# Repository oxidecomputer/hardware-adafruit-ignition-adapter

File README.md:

# hardware-adafruit-ignition-adapter

## Description

Adapter board for the [Adafruit FT232H](https://www.adafruit.com/product/2264)
compatible with `iceprog` and the Samtec debug pinout we're using on our
designs.

## Ordering Information

Each release contains a file called `[CPN]_release_notes.txt` with ordering
instructions. Order PCBs through Sierra Circuits' [Turnkey
PRO](https://www.protoexpress.com/products/turnkey-pro/) fabrication and
assembly service.

## Release Information

Fabrication data follows the `[CPN]_rev[X]_v[Y]` naming convention, where
revision `rev[X]` and version `v[Y]` corresponds to the two numbers in Altium's
release version. Here's why:

- When we release the board in Altium 365, Altium tags the release with the
  suffix `[X].[Y]`

- However, Sierra Circuits only accepts a single revision number, which appears
  in their ordering system as `_rev[X]`.
  
- When we assemble the tapeout data package together for Sierra Circuits, we
  name the tapeout files `[CPN]_rev[X]_v[Y]` to maintain the mapping between
  Altium release and the out-of-band tapeout data package.

- When we order PCBs through Sierra Circuits, we specify the revision using the
  `[X]` number. This appears in Sierra's order system as `[CPN]_rev[X]`.

Essentially, we ignore the `[Y]` value and we increment the `[X]` in the Altium
release. In practice, however, the `[Y]` value in the Altium release ends up
getting incremented if we have to re-release something in Altium to correct data
export errors before submitting the release for fabrication (for example, to fix
missing drill files in the tapeout data package). If this sounds confusing, it's
because it is.

## Assembly

Follow the [assembly
instructions](https://github.com/oxidecomputer/hardware-adafruit-ignition-adapter/tree/main/assembly)
to assemble a complete Ignition programming dongle.

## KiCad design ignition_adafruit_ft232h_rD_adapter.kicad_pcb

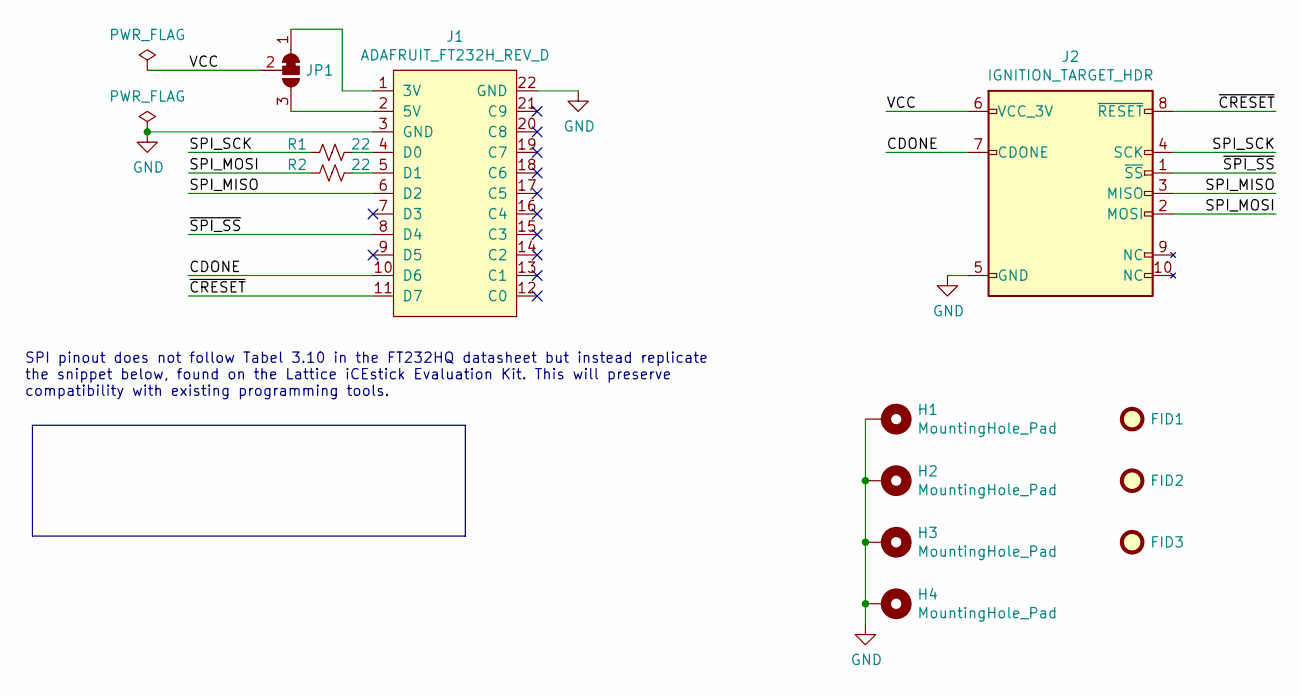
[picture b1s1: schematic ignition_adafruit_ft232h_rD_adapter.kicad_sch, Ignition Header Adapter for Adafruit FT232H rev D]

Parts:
FID1, FID3: Fiducial; Fiducial_0.5mm_Mask1mm
FID2: iCE40 Adapter; Oxide_Board_Identifier_23x6mm
H1, H2, H3, H4: MountingHole_Pad; MountingHole_100mils_Pad
J1: ADAFRUIT_FT232H_REV_D; ADAFRUIT_FT232H_REVD
J2: IGNITION_TARGET_HDR; TFC-105-02-F-D-A-K
JP1: SolderJumper_3_Bridged12; SolderJumper-3_P1.3mm_Bridged12_Pad1.0x1.5mm
R1, R2: 22; R_0603_1608Metric

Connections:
/CDONE: J1.10 (D6), J2.7 (CDONE)
/SPI_MISO: J1.6 (D2), J2.3 (MISO)
/SPI_MOSI: J2.2 (MOSI), R2.2
/SPI_SCK: J2.4 (SCK), R1.2
/VCC: J2.6 (VCC_3V), JP1.2 (C)
/~CRESET: J1.11 (D7), J2.8 (~RESET)
/~SPI_SS: J1.8 (D4), J2.1 (~SS)
GND: H1.1, H2.1, H3.1, H4.1, J1.3 (GND), J1.22 (GND), J2.5 (GND)
unnamed: J1.1 (3V), JP1.1 (A)
unnamed: J1.2 (5V), JP1.3 (B)
unnamed: J1.4 (D0), R1.1
unnamed: J1.5 (D1), R2.1

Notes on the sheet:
SPI pinout does not follow Tabel 3.10 in the FT232HQ datasheet but instead replicate the snippet below, found on the Lattice iCEstick Evaluation Kit. This will preserve compatibility with existing programming tools.

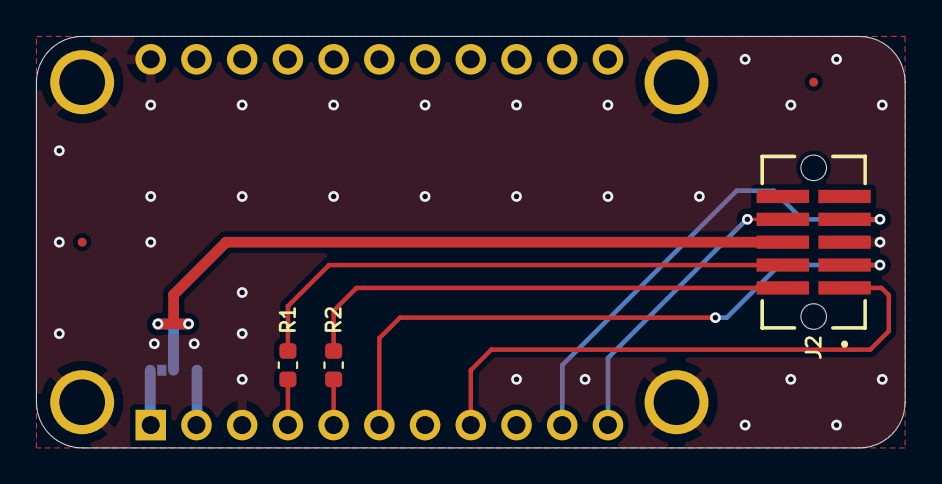
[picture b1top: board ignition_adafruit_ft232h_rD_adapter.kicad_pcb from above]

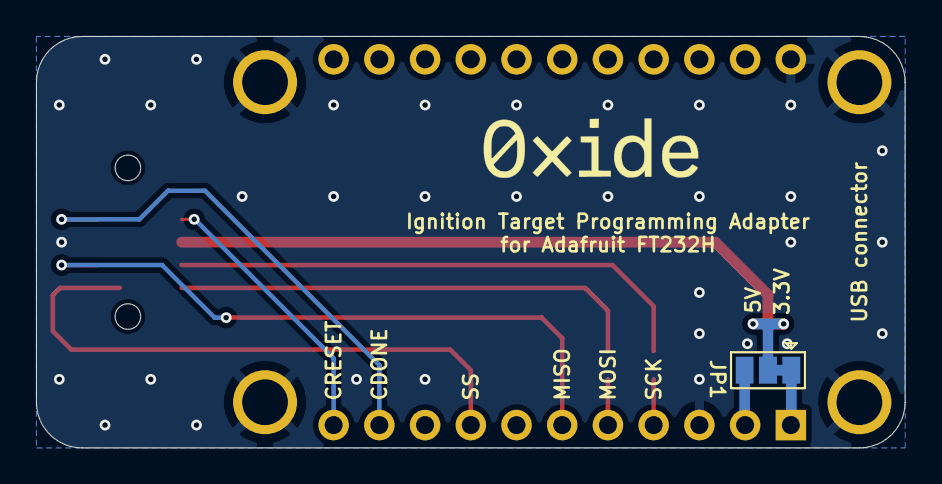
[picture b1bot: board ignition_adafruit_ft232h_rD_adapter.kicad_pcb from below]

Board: 4 copper layers, 48.3 x 22.9 mm, 12 parts (2 on the bottom side), 12 nets.

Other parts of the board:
Ref**: Val**; OXIDE_Wordmark

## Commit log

2023-02-24 Initial commit of restructured design
2023-07-10 Fixes #1, Fixes #3
2023-07-10 Fixes #5, Fixes #4
2023-07-13 Panelized design
2025-08-28 restructured project and added bom
2025-08-28 added release files
2025-08-28 renamed release files for consistency
2025-08-29 added missing drill files and regenerated TDP
2025-09-25 released rev2 v2
2025-10-02 created first-pass assembly instructions and restructured release files
2025-10-02 updating ordering and release information
2025-10-02 updated assembly instructions
